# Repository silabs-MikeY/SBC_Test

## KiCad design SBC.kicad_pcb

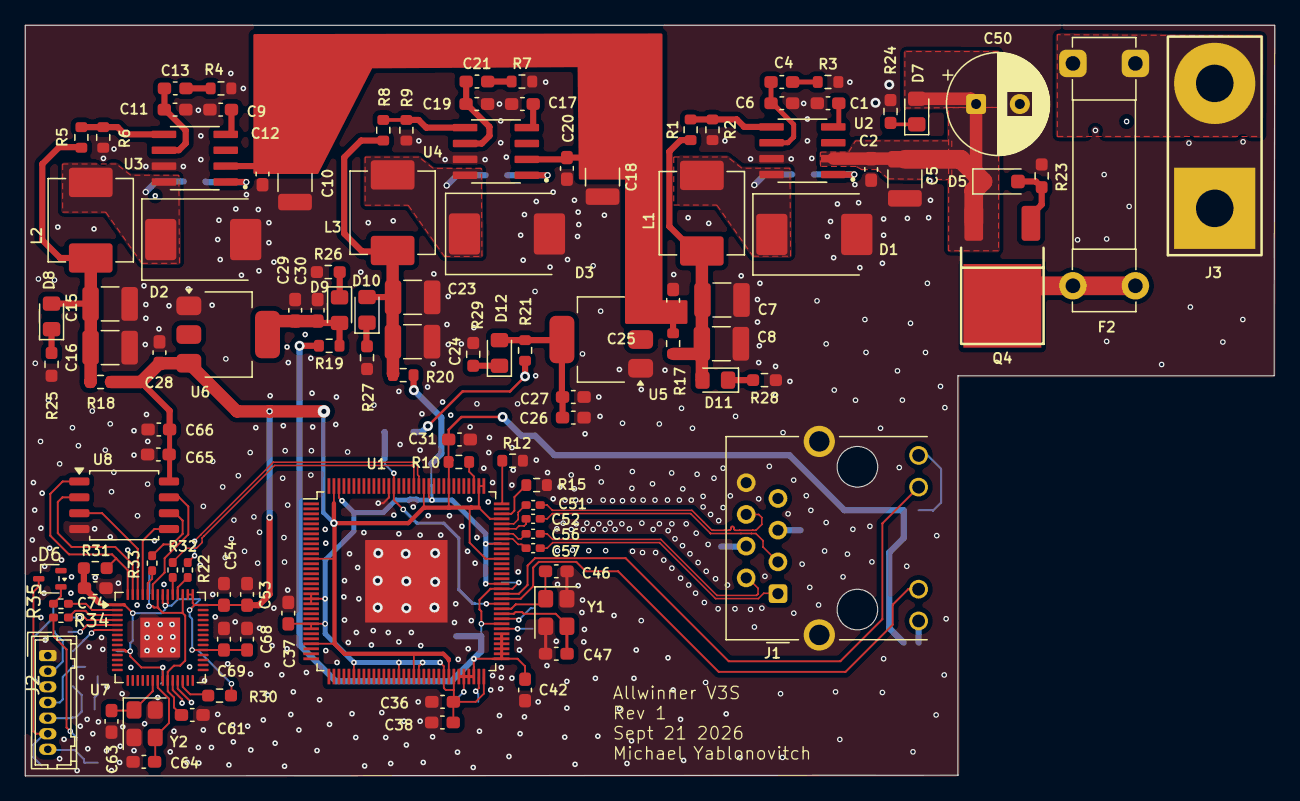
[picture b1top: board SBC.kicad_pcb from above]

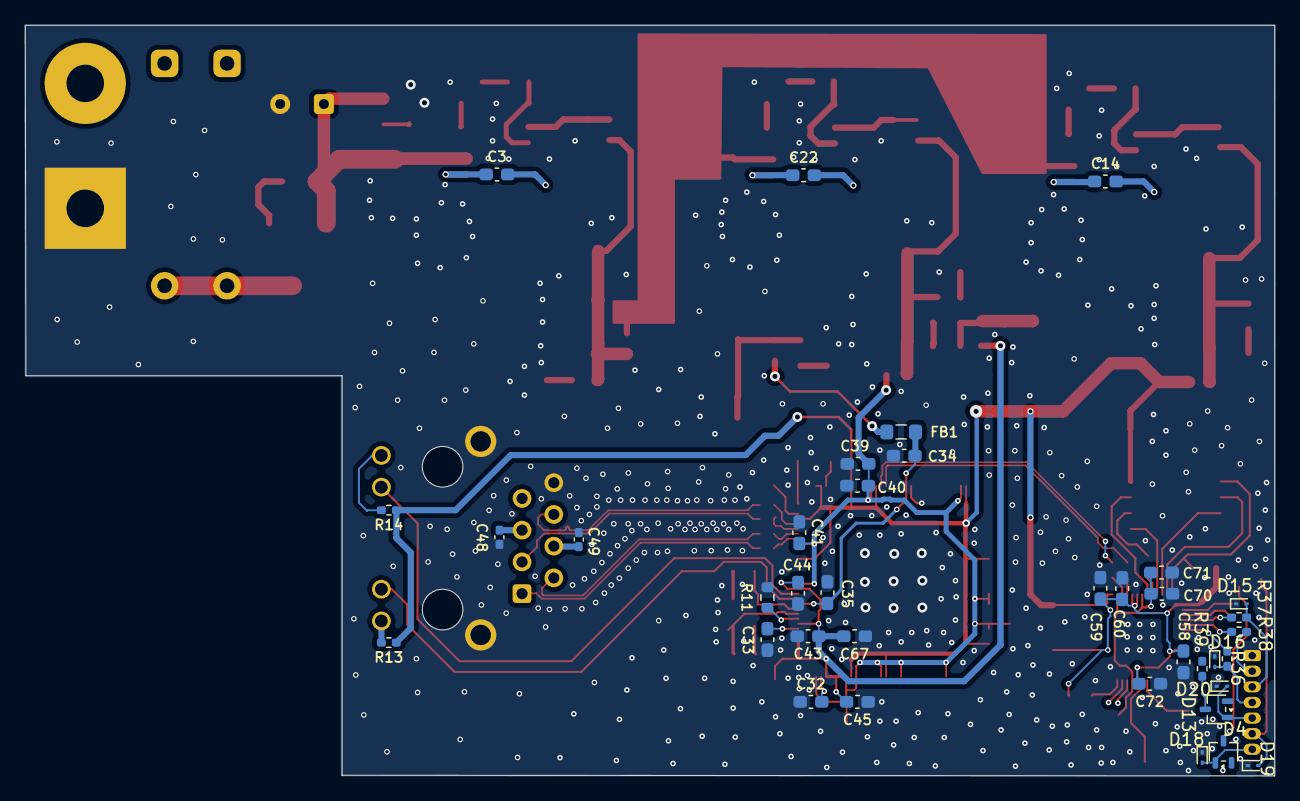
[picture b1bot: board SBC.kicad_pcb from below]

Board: 4 copper layers, 100.0 x 60.1 mm, 146 parts (37 on the bottom side), 91 nets.

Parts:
C1, C9, C17, C21: 10n; C_0603_1608Metric_Pad1.08x0.95mm_HandSolder
C2, C3, C12, C14, C20, C22, C32, C33, C34, C35, C36, C37, C40, C41, C42, C43, C44, C45, C54, C58, C60, C61, C65, C69, C70, C72, C74: 100n; C_0603_1608Metric_Pad1.08x0.95mm_HandSolder
C4: 3n3; C_0603_1608Metric_Pad1.08x0.95mm_HandSolder
C5, C10, C18: 10u; C_1210_3225Metric_Pad1.33x2.70mm_HandSolder
C6, C11: 47p; C_0603_1608Metric_Pad1.08x0.95mm_HandSolder
C7, C8, C15, C16, C23, C24: 47u; C_1210_3225Metric_Pad1.33x2.70mm_HandSolder
C13: 4n7; C_0603_1608Metric_Pad1.08x0.95mm_HandSolder
C19: 100p; C_0603_1608Metric_Pad1.08x0.95mm_HandSolder
C25, C27, C28, C29, C31, C53, C59, C66, C68, C71: 1u; C_0603_1608Metric_Pad1.08x0.95mm_HandSolder
C26, C30: 10u; C_0603_1608Metric_Pad1.08x0.95mm_HandSolder
C38, C39, C67: 4u7; C_0603_1608Metric_Pad1.08x0.95mm_HandSolder
C46, C47: 36p; C_0603_1608Metric_Pad1.08x0.95mm_HandSolder
C48, C49: 100n; C_0402_1005Metric_Pad0.74x0.62mm_HandSolder
C50: 100u; CP_Radial_D8.0mm_P3.50mm
C51, C52, C56, C57: 10n; C_0402_1005Metric_Pad0.74x0.62mm_HandSolder
C63, C64: 15p; C_0603_1608Metric_Pad1.08x0.95mm_HandSolder
D1, D2, D3: MBRS340; D_SMC
D4, D6, D13: BAT54W; SOT-323_SC-70
D5: BZT52C10; D_SOD-123F
D7, D8, D9, D10, D11, D12: LED; LED_0805_2012Metric_Pad1.15x1.40mm_HandSolder
D15, D16, D18, D19, D20: ESD9B3.3ST5G; D_SOD-923
F2: Fuse; Fuseholder_Clip-5x20mm_Bel_FC-203-22_Lateral_P17.80x5.00mm_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
FB1: 600r @ 100MHz; L_0805_2012Metric_Pad1.05x1.20mm_HandSolder
J1: HR911105A; RJ45_Hanrun_HR911105A_Horizontal
J2: Conn_01x07_Socket; Hirose_DF13-07P-1.25DSA_1x07_P1.25mm_Vertical
J3: Wire_Solder_2Pin; Wire_Solder_2Pin_12-14AWG_P10mm_D3.0mm
L1: 10u; L_Changjiang_FXL0630
L2: 6u8; L_Changjiang_FXL0630
L3: 3u3; L_Changjiang_FXL0630
Q4: DOD40P03; DOD40P03_TO-252_Q_PMOS_DGS
R1, R3, R5, R8, R10: 10k2; R_0603_1608Metric
R2: 1k87; R_0603_1608Metric
R4: 6k8; R_0603_1608Metric
R6: 3k24; R_0603_1608Metric
R7: 3k3; R_0603_1608Metric
R9: 20k5; R_0603_1608Metric
R11: 240r; R_0603_1608Metric
R12: 10k; R_0603_1608Metric
R13, R14: 330r; R_0402_1005Metric_Pad0.72x0.64mm_HandSolder
R15: 3k01; R_0603_1608Metric
R17, R18, R19, R20, R21: 0r; R_0603_1608Metric
R22, R32: 27r; R_0402_1005Metric_Pad0.72x0.64mm_HandSolder
R23, R24, R25, R26, R27, R28, R29, R30, R31: 10k; R_0603_1608Metric_Pad0.98x0.95mm_HandSolder
R33: 10r; R_0402_1005Metric_Pad0.72x0.64mm_HandSolder
R34, R35, R36, R37, R38, R39: 100r; R_0402_1005Metric_Pad0.72x0.64mm_HandSolder
U1: Allwinner_V3s; eLQFP-128_14x14_Pitch0.4mm_EPAD_6.60mm
U2, U3, U4: TPS54331DR; SOIC127P599X175-8N
U5: TLV1117-33; SOT-223-3_TabPin2
U6: TLV1117-18; SOT-223-3_TabPin2
U7: RP2040; QFN-56-1EP_7x7mm_P0.4mm_EP3.2x3.2mm
U8: W25Q16JVSS; SOIC-8_5.3x5.3mm_P1.27mm
Y1, Y2: Crystal_GND24; Crystal_SMD_3225-4Pin_3.2x2.5mm

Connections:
+1V2: C36.2, C37.2, C38.2, C39.2, C40.2, C41.2, R20.2, U1.19 (VDD-SYS3), U1.20 (VDD-CPU3), U1.21 (VDD-CPU2), U1.25 (VDD-CPU1), U1.26 (VDD-CPU0), U1.38 (VDD-CPU4), U1.47 (VDD-CPU5), U1.51 (VDD-CPU6), U1.56 (VDD-CPU7), U1.58 (VDD-SYS4), U1.64 (VDD-SYS5), U1.80 (VDD-SYS0), U1.88 (EPHY-VDD), U1.108 (VDD-SYS1), U1.126 (VDD-SYS2)
+1V8: C42.2, C43.2, C44.2, C45.2, C67.2, R19.2, U1.59 (VCC-DRAM8), U1.60 (VCC-DRAM9), U1.61 (VCC-DRAM10), U1.62 (VCC-DRAM11), U1.65 (VCC-DRAM0), U1.66 (VCC-DRAM1), U1.67 (VCC-DRAM2), U1.68 (VCC-DRAM3), U1.69 (VCC-DRAM4), U1.70 (VCC-DRAM5), U1.72 (VCC-DRAM6), U1.79 (VCC-DRAM7)
+3.3V: C28.2, C31.2, C53.2, C54.2, C58.2, C59.2, C60.2, C65.2, C66.2, C68.2, C69.2, C72.2, C74.2, R10.1, R13.1, R14.1, R18.2, R30.2, R31.2, U1.12 (VCC-PE0), U1.29 (VCC-PE1), U1.50 (VCC-IO3(PG)), U1.57 (VCC-IO2(PF)), U1.85 (VCC-MCSI), U1.93 (EPHY-VCC), U1.97 (RTC-VIO), U1.98 (VCC-RTC), U1.104 (VCC-IO0(PB)), U1.109 (VCC-USB), U1.127 (VCC-IO1(PC)), U6.3 (VI), U7.1 (IOVDD), U7.10 (IOVDD), U7.22 (IOVDD), U7.33 (IOVDD), U7.42 (IOVDD), U7.43 (ADC_AVDD), U7.44 (VREG_VIN), U7.48 (USB_VDD), U7.49 (IOVDD), U8.8 (VCC)
+3.3VA: FB1.1, R21.2
+5V: C10.1, C12.1, C18.1, C20.1, C25.2, R17.2, U3.2 (VIN), U4.2 (VIN), U5.3 (VI)
+12V: C2.1, C5.1, C50.1, D5.1 (K), D7.2 (A), Q4.3 (S), U2.2 (VIN)
/Ethernet/RX+: C52.1, J1.3
/Ethernet/RX-: C51.1, J1.6
/Ethernet/TX+: C57.1, J1.1
/Ethernet/TX-: C56.1, J1.2
E_RXN: C57.2, U1.89 (EPHY-RXN)
E_RXP: C56.2, U1.90 (EPHY-RXP)
E_TXN: C52.2, U1.91 (EPHY-TXN)
E_TXP: C51.2, U1.92 (EPHY-TXP)
GND: C1.2, C2.2, C5.2, C6.2, C7.2, C8.2, C9.2, C10.2, C11.2, C12.2, C15.2, C16.2, C17.2, C18.2, C19.2, C20.2, C23.2, C24.2, C25.1, C26.1, C27.1, C28.1, C29.1, C30.1, C31.1, C32.1, C33.1, C34.1, C35.1, C36.1, C37.1, C38.1, C39.1, C40.1, C41.1, C42.1, C43.1, C44.1, C45.1, C46.1, C47.1, C48.2, C49.2, C50.2, C53.1, C54.1, C58.1, C59.1, C60.1, C61.1, C63.2, C64.2, C65.1, C66.1, C67.1, C68.1, C69.1, C70.1, C71.1, C72.1, C74.1, D1.2 (A), D2.2 (A), D3.2 (A), D15.1 (A1), D16.1 (A1), D18.1 (A1), D19.1 (A1), D20.1 (A1), J1.8, J1.SH, J2.1, J3.1 (WIRE1), R2.2, R3.2, R4.2, R6.2, R7.2, R9.2, R11.2, R12.2, R15.2, R23.1, R24.1, R25.1, R26.1, R27.1, R28.1, R29.1, U1.116 (AGND), U1.EPAD (EGND), U2.7 (GND), U3.7 (GND), U4.7 (GND), U5.1 (GND), U6.1 (GND), U7.57 (GND), U8.4 (GND), Y1.2 (G), Y1.4 (G), Y2.2 (G), Y2.4 (G)
unnamed: C4.2, R3.1
unnamed: C13.2, R4.1
unnamed: C21.2, R7.1
unnamed: C48.1, J1.5
unnamed: C49.1, J1.4
unnamed: C3.2, D1.1 (K), L1.1, U2.8 (PH)
unnamed: C14.2, D2.1 (K), L2.1, U3.8 (PH)
unnamed: C22.2, D3.1 (K), L3.1, U4.8 (PH)
unnamed: D4.3 (K), R34.2
unnamed: D5.2 (A), Q4.2 (G), R23.2
unnamed: D6.1 (A), R35.2
unnamed: D7.1 (K), R24.2
unnamed: C15.1, C16.1, D8.2 (A), L2.2, R5.1, R18.1
unnamed: D8.1 (K), R25.2
unnamed: C29.2, C30.2, D9.2 (A), R19.1, U6.2 (VO)
unnamed: D9.1 (K), R26.2
unnamed: C23.1, C24.1, D10.2 (A), L3.2, R8.1, R20.1
unnamed: D10.1 (K), R27.2
unnamed: C7.1, C8.1, D11.2 (A), L1.2, R1.1, R17.1
unnamed: D11.1 (K), R28.2
unnamed: C26.2, C27.2, D12.2 (A), R21.1, U5.2 (VO)
unnamed: D12.1 (K), R29.2
unnamed: D13.1 (A), D20.2 (A2), J2.5
unnamed: D13.3 (K), R39.2
unnamed: D15.2 (A2), J2.3, R37.2
unnamed: D16.2 (A2), J2.4, R36.2
unnamed: D4.1 (A), D18.2 (A2), J2.7
unnamed: D6.3 (K), D19.2 (A2), J2.6
unnamed: J1.9, R13.2
unnamed: J1.12, R14.2
unnamed: J2.2, R38.2
unnamed: F2.1, J3.2 (WIRE2)
unnamed: F2.2, Q4.1 (D)
unnamed: R15.1, U1.94 (EPHY-RTX)
unnamed: C34.2, C35.2, FB1.2, U1.76 (VCC-PLL), U1.115 (AVCC)
unnamed: C33.2, U1.71 (SVREF0)
unnamed: C32.2, U1.63 (SVREF1)
unnamed: R11.1, U1.73 (SZQ)
unnamed: C46.2, U1.75 (X24MIN), Y1.1
unnamed: C47.2, U1.74 (X24MOUT), Y1.3
unnamed: R12.1, U1.96 (X32KIN)
unnamed: R10.2, U1.99 (~RESET)
unnamed: C3.1, U2.1 (BOOT)
unnamed: C4.1, C6.1, U2.6 (COMP)
unnamed: C1.1, U2.4 (SS)
unnamed: R1.2, R2.1, U2.5 (VSENSE)
unnamed: C14.1, U3.1 (BOOT)
unnamed: C11.1, C13.1, U3.6 (COMP)
unnamed: C9.1, U3.4 (SS)
unnamed: R5.2, R6.1, U3.5 (VSENSE)
unnamed: C22.1, U4.1 (BOOT)
unnamed: C19.1, C21.1, U4.6 (COMP)
unnamed: C17.1, U4.4 (SS)
unnamed: R8.2, R9.1, U4.5 (VSENSE)
unnamed: R33.2, U7.52 (QSPI_SCLK)
unnamed: U7.53 (QSPI_SD0), U8.5 (DI/IO_{0})
unnamed: U7.55 (QSPI_SD1), U8.2 (DO/IO_{1})
unnamed: U7.54 (QSPI_SD2), U8.3 (~WP/IO_{2})
unnamed: U7.51 (QSPI_SD3), U8.7 (~HOLD/~RESET/IO_{3})
unnamed: R30.1, U7.26 (RUN)
unnamed: R22.2, U7.46 (USB_DM)
unnamed: R32.2, U7.47 (USB_DP)
unnamed: C61.2, C70.2, C71.2, U7.23 (DVDD), U7.45 (VREG_VOUT), U7.50 (DVDD)
unnamed: C63.1, U7.20 (XIN), Y2.1
unnamed: C64.1, U7.21 (XOUT), Y2.3
unnamed: R31.1, U7.56 (~QSPI_SS), U8.1 (~CS)
unnamed: R33.1, U8.6 (CLK)
PHY_ACTIVITY: J1.11, U1.78 (EPHY-SPD-LED)
PHY_LINK: J1.10, U1.77 (EPHY-LINK-LED)
RESET: R36.1, U7.6 (GPIO4)
RX: R34.1, U7.3 (GPIO1)
SWCLK: R37.1, U7.4 (GPIO2)
SWDIO: R38.1, U7.5 (GPIO3)
TX: R35.1, U7.2 (GPIO0)
USB_DN: R22.1, U1.110 (USB-DM)
USB_DP: R32.1, U1.111 (USB-DP)

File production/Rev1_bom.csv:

Designator,Footprint,Quantity,Value,LCSC Part #
"C1, C17, C21, C9",0603,4,10n,C100042
"C10, C18, C5",1210,3,10u,C2909422
"C11, C6",0603,2,47p,C105622
"C12, C14, C2, C20, C22, C3, C32, C33, C34, C35, C36, C37, C40, C41, C42, C43, C44, C45, C54, C58, C60, C61, C65, C69, C70, C72, C74",0603,27,100n,C1591
C13,0603,1,4n7,C106218
"C15, C16, C23, C24, C7, C8",1210,6,47u,C596320
C19,0603,1,100p,C14665
"C25, C27, C28, C29, C31, C53, C59, C66, C68, C71",0603,10,1u,C14664
"C26, C30",0603,2,10u,C14664
"C38, C39, C67",0603,3,4u7,C296042
C4,0603,1,3n3,C107088
"C46, C47",0603,2,36p,C519462
"C48, C49",0402,2,100n,C131394
C50,CP_Radial_D8.0mm_P3.50mm,1,100u,C171434
"C51, C52, C56, C57",0402,4,10n,C60133
"C63, C64",0603,2,15p,C107037
"D1, D2, D3",D_SMC,3,MBRS340,C3759261
"D10, D11, D12, D7, D8, D9",0805,6,LED,C110099
"D13, D4, D6",SOT-323_SC-70,3,BAT54W,C8657
"D15, D16, D18, D19, D20",D_SOD-923,5,ESD9B3.3ST5G,C3040608
D5,D_SOD-123F,1,BZT52C10,C571378
F2,Fuseholder_Clip-5x20mm_Bel_FC-203-22_Lateral_P17.80x5.00mm_D1.17mm_Horizontal,1,Fuse,C3205463
FB1,0805,1,600r @ 100MHz,C341663
J1,RJ45_Hanrun_HR911105A_Horizontal,1,HR911105A,C12074
J2,Hirose_DF13-07P-1.25DSA_1x07_P1.25mm_Vertical,1,Conn_01x07_Socket,C17565513
L1,L_Changjiang_FXL0630,1,10u,C167223
L2,L_Changjiang_FXL0630,1,6u8,C167222
L3,L_Changjiang_FXL0630,1,3u3,C167220
Q4,DOD40P03_TO-252_Q_PMOS_DGS,1,DOD40P03,C36499177
"R1, R10, R3, R5, R8",0603,5,10k2,C22772
R11,0603,1,240r,C23350
R12,0603,1,10k,C25804
"R13, R14",0402,2,330r,C25104
R15,0603,1,3k01,C22991
"R17, R18, R19, R20, R21",0603,5,0r,C21189
R2,0603,1,1k87,C22850
"R22, R32",0402,2,27r,C25099
"R23, R24, R25, R26, R27, R28, R29, R30, R31",0603,9,10k,C98220
R33,0402,1,10r,C25077
"R34, R35, R36, R37, R38, R39",0402,6,100r,C25076
R4,0603,1,6k8,C23212
R6,0603,1,3k24,C22994
R7,0603,1,3k3,C22978
R9,0603,1,20k5,C22910
U1,eLQFP-128_14x14_Pitch0.4mm_EPAD_6.60mm,1,Allwinner_V3s,
"U2, U3, U4",SOIC127P599X175-8N,3,TPS54331DR,C9865
U5,SOT-223-3_TabPin2,1,TLV1117-33,C37359
U6,SOT-223-3_TabPin2,1,TLV1117-18,C2862410
U7,QFN-56-1EP_7x7mm_P0.4mm_EP3.2x3.2mm,1,RP2040,C2040
U8,SOIC-8_5.3x5.3mm_P1.27mm,1,W25Q16JVSS,C131025
Y1,Crystal_SMD_3225-4Pin_3.2x2.5mm,1,Crystal_GND24,C12260
Y2,Crystal_SMD_3225-4Pin_3.2x2.5mm,1,Crystal_GND24,C13738
